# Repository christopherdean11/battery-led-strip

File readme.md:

# Battery Boost LED Strip Driver
This repo contains the Kicad project files for a PCB to boost a 4-AA battery bank up to 12V to drive an LED tape strip. 

## Goal
Deisgn a PCB to power a 12V LED strip in a closet that turns on when the door opens and off when the door closes, in an area where there are no outlets availble for wall power.

## LED Tape Strip
I selected this LED tape strip from HitLights, model number: `L0512V-401-1630-U`.
Some quick information about these LEDs:  
* 16.4ft long, can be cut to length every 2 inches
* Runs on 12V
* 24W to power the full strip. This works out to 2A for the full strip, or 20 mA per cuttable 2 inch segment
* 4000 K LED color (this felt like a good compromise for a closet between 2700 K or 3000 K which is a warm white, and 5000 K "daylight" which is usually a bit harsh for me)

## PCB Rev0
See [Rev0 Design Notes](BatteryLedStripDriver-R0/readme.md)  
Here is a gif demonstrating the circuit on a short strip of LEDs

Here are some [ideas for a future revision](BatteryLedStripDriver-R0/readme.md#next-gen-ideas)

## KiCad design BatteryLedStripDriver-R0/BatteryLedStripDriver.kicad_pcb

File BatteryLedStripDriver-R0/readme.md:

# PCB Rev0
The first attempat at a PCB to boost 4-AA batteries to driver 12V LED strip.

Here is the board next to a AA battery.  

## Design
See the [schematic print](Outputs/BatteryLedStripDriver.pdf). Key elements include:  
#### Boost converter
*  `TPS55340PWP` to boost ~6V (with new batteries) to 12V. Needed something with a high enough current limit on the power switch to support 1A out at a duty cycle of 4V->12V, plus wanted it in stock at JLCPCB. This one matched those criteria and had the added benefit of TI's WEBENCH tool support.
#### PWM signal generator
* 555 timer `TLC555xD` for optional PWM dimming, with potentiometer to set duty cycle. Here's an [article with 555 timer circuits](https://www.electronics-tutorials.ws/waveforms/555-circuits-part-1.html) that I referred to while adding this to the schematic. 
#### PMOS pass transistors
* `DMP2305U` to switch the boost converter and 555 timer input power on door open/close. Using PMOS because I didn't want to get into charge pumps to drive NMOS transistors. This one is rated for max Vds of -20V, max drain current of -4A, and Rdson of 60mΩ when pulling Vgs to -4.5V. 
#### Reed switch
* Found a [reed switch with both NC and NO options](https://www.amazon.com/dp/B073Z7TQ5D), which meant I couldn't mess up the order and get the wrong type :)
* This will be used to detect the door open/close state
* I added a small circuit to deal with the reed switch as NO or NC, selected by a jumper. This NC/NO combined switch was great for testing that circuit. 
#### Other Notes
* Some sections are tied together with 0 ohm resistors in case anything didn't work it could be excluded by removing a resistor instead of removing the whole IC. 
* I wasn't sure how well PWM-ing the boost converter output would work since it would effectively be seen as continuous load transients. Normally you would want to tie the EN pin of the DC/DC with the PWM signal, but this boost converter has an EN falling delay of 1ms before disabling, but it was hard enough to find this one to use, so I just went for it. I figured the lights would dim but the output voltage might be a bit ugly on the oscilloscope.
* Followed [Phil's Lab video](https://www.youtube.com/watch?v=C7-8nUU6e3E) on how to take a Kicad project to JLCPCB for fabrication and assembly. Some of the process is slightly updated since the video was made but it was easy enough to use, in fact the JLC website has a great in-browser experience for adjusting the part rotations that wasn't available at the time the video was filmed. 

## Bring up notes
#### Missing Pulldown
* Found a missed pulldown resistor on the gate of Q1 while reviewing the schematic again before the board arrived
  * This proved to in fact be an issue where the reed switch would not induce a state change unless it was probed with the oscilloscope, presumably adding a small leakage path to ground.  

  * Added 100k from Q1 gate (pin 1) to GND. I had a 100k through-hole on hand, so I tied it from SW1 pin 1 to the unmasked mounting hole, since the mounting holes were tied to GND (for easy oscillocope probe GND clip spots).   
        
    The net with the gate of Q1 is highlighted in the PCB image below, showing where the resistor was added between the SW1 jumper pin and GND pad of the mounting hole.

  * :white_check_mark: With the pulldown in place the board turns on/off with the reed switch as desired! :) 
* All of the following test notes assume the Q1 pulldown is in place.

#### Enable
* :white_check_mark: Tested NO and NC enable modes (with the appropriate NO or NC reed switch connection), both turn on the output when the reed swith is opened/separated (i.e. the door is opened), so the invert/no-invert circuit works as desired. 
#### PWM
* Tested with two 1k resistors in parallel to get 12V/500ohm = 24mA load
* Can PWM up to 100% duty cycle and down to less than 5%
* Output waveform is not nice and square, has a 2.5-3V dip on PWM rising edge, likely because of the load transient caused by PWM-ing the load without disabling the power converter. 
* :white_check_mark: The LEDs can be dimmed from full brigthness down to almost off.

#### End-to-End Test
* :white_check_mark: Battery bank + PCB + short LED strip + Reed switch, works as desired :)

* :white_check_mark: Full test with battery bank and 2 ft. LED strip works!   
* There is an audible buzzing/humming when dimming the LEDs while drawing high current (longer strip) due to PWM-ing the output, and most likely [causing the cermaic output capacitors to vibrate against the PCB](https://www.murata.com/en-us/products/capacitor/ceramiccapacitor/library/apps/notepc) in the audio frequency band due to the low PWM frequency. Going to 100% duty cycle eliminates the noise. 

## Installation
Here it is installed above the door inside the previous very dark closet.  
    
I have 1980's textured ceiling/walls inside the closet, so I stuck the LED strip to the thinnest peice of wood I had on hand, zip-tied the battery holder and PCB to another peice of wood, and attched each with some screws into the drywall. 
The reed switch and magnet are mounted at the top of the doorway and the door. 

## Next-Gen Ideas
A few thoughts that came up to include for a next revision:
* Add an MCU 
  - More flexible PWM generation
  - Timer to shut off the lights if door is left open
  - Battery monitoring with some kind of indicator for low battery (such as blinking the LEDs once or twice at power-on)
* Different power converter
  - One that supports PWM-ing the EN pin. May need to try using a LED driver IC and 'trick' it into constant voltage mode 
  - Consider a buck-boost. This could allow for multiple output voltage levels for different LED strips. I've seen 5V and 6V strips as well as the typical 12V strip. Some go up to 24V but boosting 6V to 24V *and* getting near 1A out would be a lot of amps at the input. 
* I would love to get some kind of single, full enclosure solution
* Connectors instead of terminal jacks. Terminal jacks are great for protyping but not great for actual long-term installation.

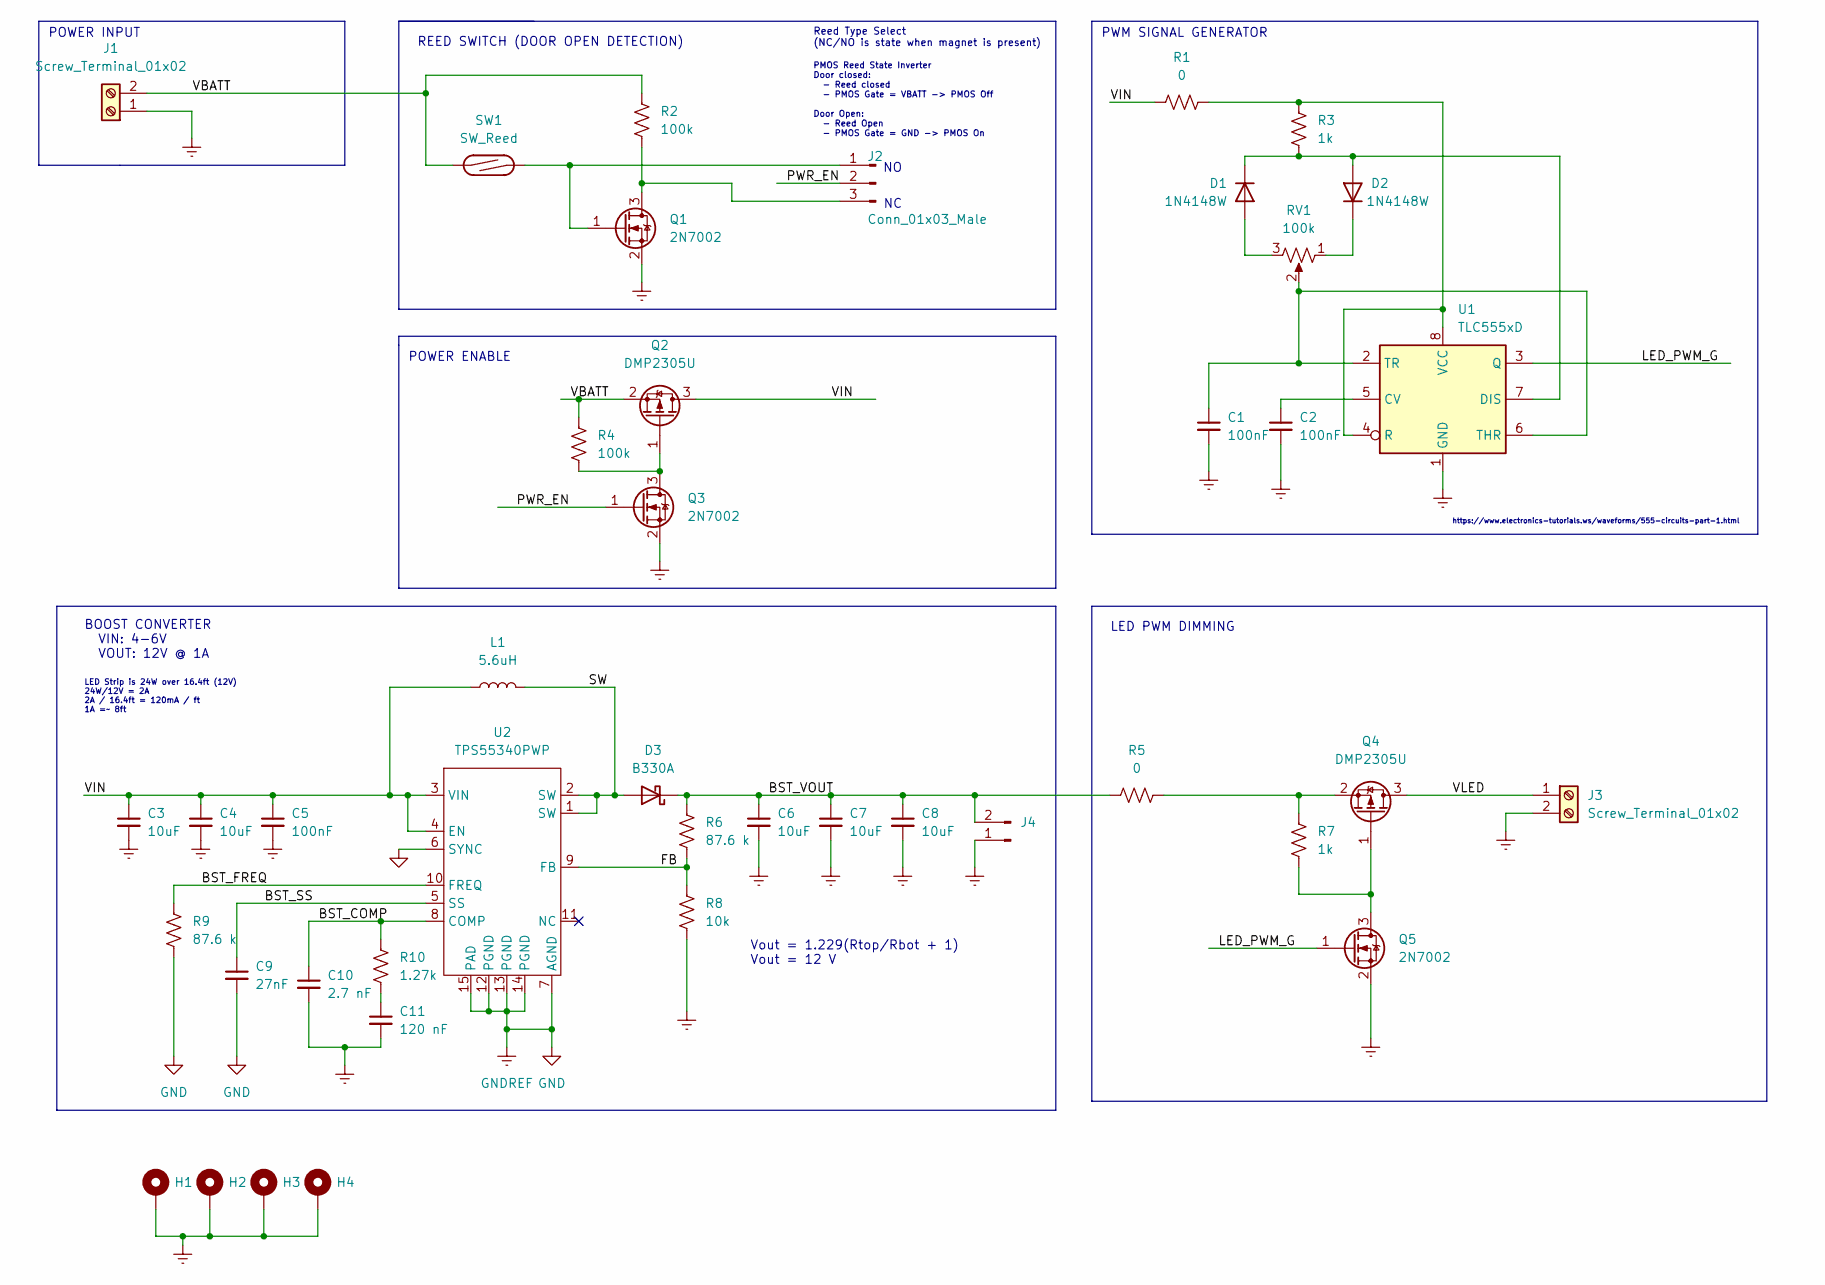
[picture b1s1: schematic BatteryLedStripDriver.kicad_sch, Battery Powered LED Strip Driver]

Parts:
C1, C2: 100nF; C_0603_1608Metric; LCSC Part # C14663
C3, C4: 10uF; C_0603_1608Metric; LCSC Part # C96446
C5: 100nF; C_0402_1005Metric; LCSC Part # C1525
C6, C7, C8: 10uF; C_0805_2012Metric; LCSC Part # C15850
C9: 27nF; C_0402_1005Metric; LCSC Part # C387951
C10: 2.7 nF; C_0402_1005Metric; LCSC Part # C387950
C11: 120 nF; C_0402_1005Metric; LCSC Part # C426033
D1, D2: 1N4148W; D_SOD-123; LCSC Part # C81598
D3: B330A; D_SMA; LCSC Part # C110485
H1, H2, H3, H4: MountingHole_Pad; MountingHole_2.7mm_M2.5_Pad
J1, J3: Screw_Terminal_01x02; TerminalBlock_Phoenix_MKDS-1,5-2_1x02_P5.00mm_Horizontal; LCSC Part # C474881
J2: Conn_01x03_Male; PinHeader_1x03_P2.54mm_Vertical
J4: Conn_01x02_Male; PinHeader_1x02_P2.54mm_Vertical
L1: 5.6uH; L_Sunlord_MWSA0603S_8.4x3.5mm; LCSC Part # C408448
Q1, Q3, Q5: 2N7002; SOT-23; LCSC Part # C8545
Q2, Q4: DMP2305U; SOT-23; LCSC Part # C85097
R1, R5: 0; R_0805_2012Metric_Pad1.20x1.40mm_HandSolder; LCSC Part # C17477
R2, R4: 100k; R_0402_1005Metric; LCSC Part # C25741
R3, R7: 1k; R_0402_1005Metric_Pad0.72x0.64mm_HandSolder; LCSC Part # C11702
R6, R9: 87.6 k; R_0402_1005Metric_Pad0.72x0.64mm_HandSolder; LCSC Part # C477808
R8: 10k; R_0402_1005Metric_Pad0.72x0.64mm_HandSolder; LCSC Part # C25744
R10: 1.27k; R_0402_1005Metric; LCSC Part # C327364
RV1: 100k; Potentiometer_Bourns_3386P_Vertical; LCSC Part # C118965
SW1: SW_Reed; PinHeader_1x02_P2.54mm_Vertical
U1: TLC555xD; SOIC-8_3.9x4.9mm_P1.27mm; LCSC Part # C6986
U2: TPS55340PWP; HTSSOP-14-1EP_4.4x5mm_P0.65mm_EP3.4x5mm_Mask3x3.1mm_Thermal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; LCSC Part # C43862

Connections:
/BST_COMP: C10.1, R10.1, U2.8 (COMP)
/BST_FREQ: R9.1, U2.10 (FREQ)
/BST_SS: C9.1, U2.5 (SS)
/BST_VOUT: C6.1, C7.1, C8.1, D3.1 (K), J4.2, R5.1, R6.1
/FB: R6.2, R8.1, U2.9 (FB)
/LED_PWM_G: Q5.1 (G), U1.3 (Q)
/PWR_EN: J2.2, Q3.1 (G)
/SW: D3.2 (A), L1.2, U2.1 (SW), U2.2 (SW)
/VBATT: J1.2, Q2.2 (S), R2.1, R4.1, SW1.1
/VIN: C3.1, C4.1, C5.1, L1.1, Q2.3 (D), R1.1, U2.3 (VIN), U2.4 (EN)
/VLED: J3.1, Q4.3 (D)
GND: C1.2, C2.2, C3.2, C4.2, C5.2, C6.2, C7.2, C8.2, C9.2, C10.2, C11.2, H1.1, H2.1, H3.1, H4.1, J1.1, J3.2, J4.1, Q1.2 (S), Q3.2 (S), Q5.2 (S), R8.2, R9.2, U1.1 (GND), U2.6 (SYNC), U2.7 (AGND), U2.12 (PGND), U2.13 (PGND), U2.14 (PGND), U2.15 (PAD)
unnamed: C1.1, RV1.2, U1.2 (TR), U1.6 (THR)
unnamed: C2.1, U1.5 (CV)
unnamed: C11.1, R10.2
unnamed: D1.1 (K), D2.2 (A), R3.2, U1.7 (DIS)
unnamed: D1.2 (A), RV1.3
unnamed: D2.1 (K), RV1.1
unnamed: J2.1, Q1.1 (G), SW1.2
unnamed: J2.3, Q1.3 (D), R2.2
unnamed: Q2.1 (G), Q3.3 (D), R4.2
unnamed: Q4.1 (G), Q5.3 (D), R7.2
unnamed: Q4.2 (S), R5.2, R7.1
unnamed: R1.2, R3.1, U1.4 (R), U1.8 (VCC)

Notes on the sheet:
PWM SIGNAL GENERATOR
POWER INPUT
Vout = 1.229(Rtop/Rbot + 1) Vout = 12 V
LED PWM DIMMING
Reed Type Select (NC/NO is state when magnet is present)
https://www.electronics-tutorials.ws/waveforms/555-circuits-part-1.html
LED Strip is 24W over 16.4ft (12V) 24W/12V = 2A 2A / 16.4ft = 120mA / ft 1A =~ 8ft
POWER ENABLE
REED SWITCH (DOOR OPEN DETECTION)
BOOST CONVERTER VIN: 4-6V VOUT: 12V @ 1A
PMOS Reed State Inverter Door closed: - Reed closed - PMOS Gate = VBATT -> PMOS Off Door Open: - Reed Open - PMOS Gate = GND -> PMOS On

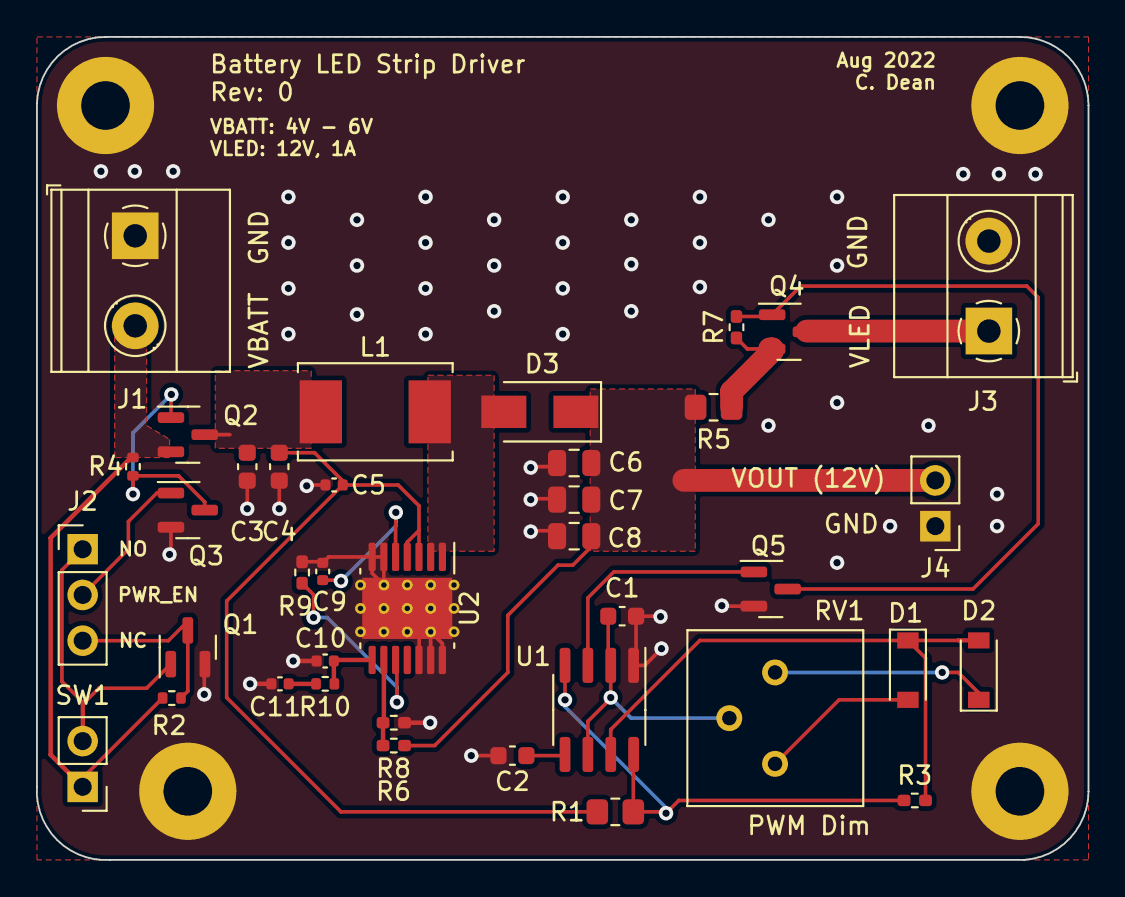
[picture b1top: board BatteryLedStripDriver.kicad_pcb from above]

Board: 2 copper layers, 58.4 x 45.7 mm, 42 parts (0 on the bottom side), 24 nets.

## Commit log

2022-08-12 initial add of PCB as fabricated
2022-08-19 fix sch typos, add/update readmes
2022-08-19 fix path to sch pdf
2022-08-19 add board image
2022-08-19 emojis
2022-09-04 add more notes and images to readme
2022-09-04 small typos/edits
2022-09-04 add next-rev ideas
